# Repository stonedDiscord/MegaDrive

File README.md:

# MegaDrive
An Open-Source HardWare (OSHW) recreation of the Sega Mega Drive

The design tries to be a 1:1 recreation of the original IC BD M5 PAL board.

## Some of the planned Changes and improvements
- [ ] Verify component values
- [ ] S-Video out

## Tips if you decide to make this/get it made
The dimensions are 240x191mm.

You will have to source the 2 SEGA custom chips from either a dead board or a chip dealer.

## Roadmap:
Look at the changes in the other revisions.

## Inspired by
https://github.com/Redherring32/OpenTendo

## Credits

ArcadeTV for the stripped scans:
https://circuit-board.de/forum/index.php/Thread/13913-STRIP-CLUB-PCB-Scans/

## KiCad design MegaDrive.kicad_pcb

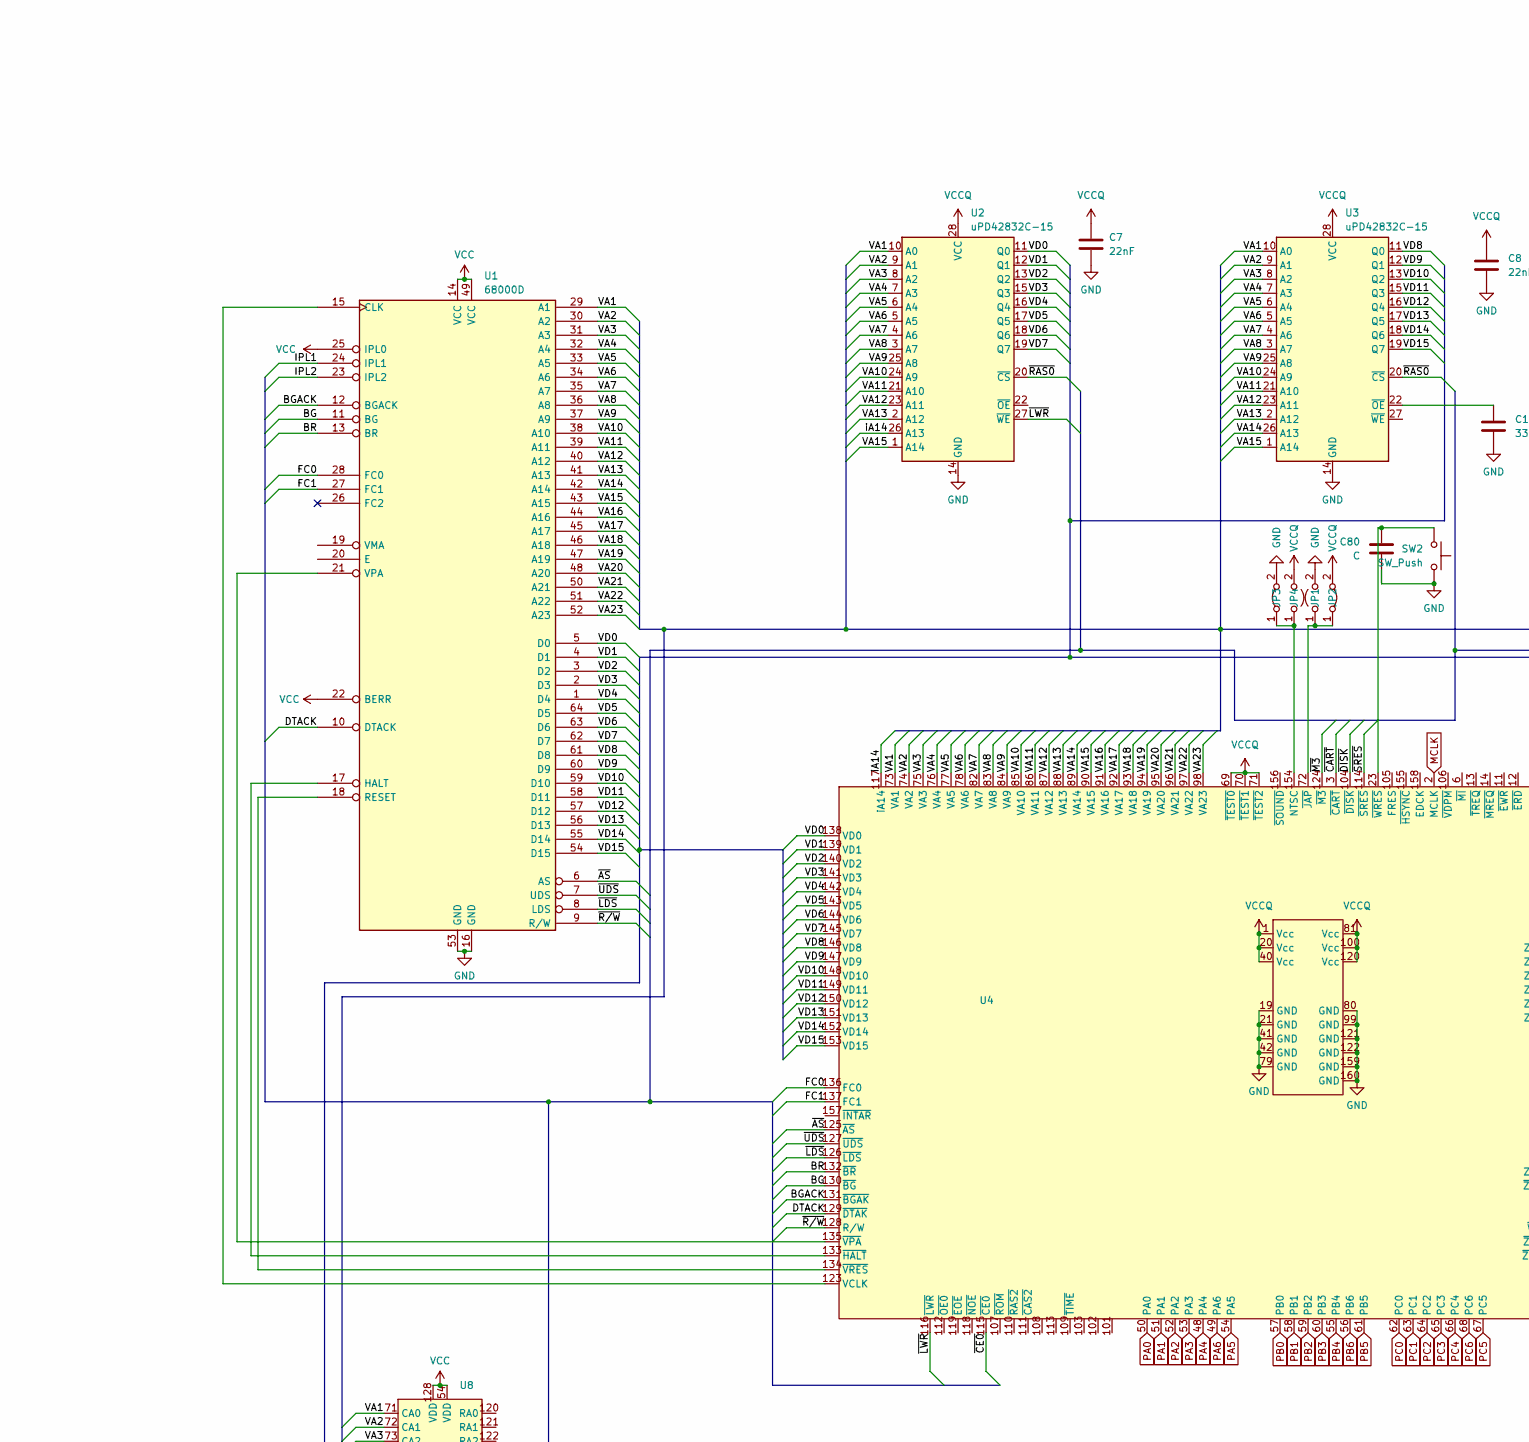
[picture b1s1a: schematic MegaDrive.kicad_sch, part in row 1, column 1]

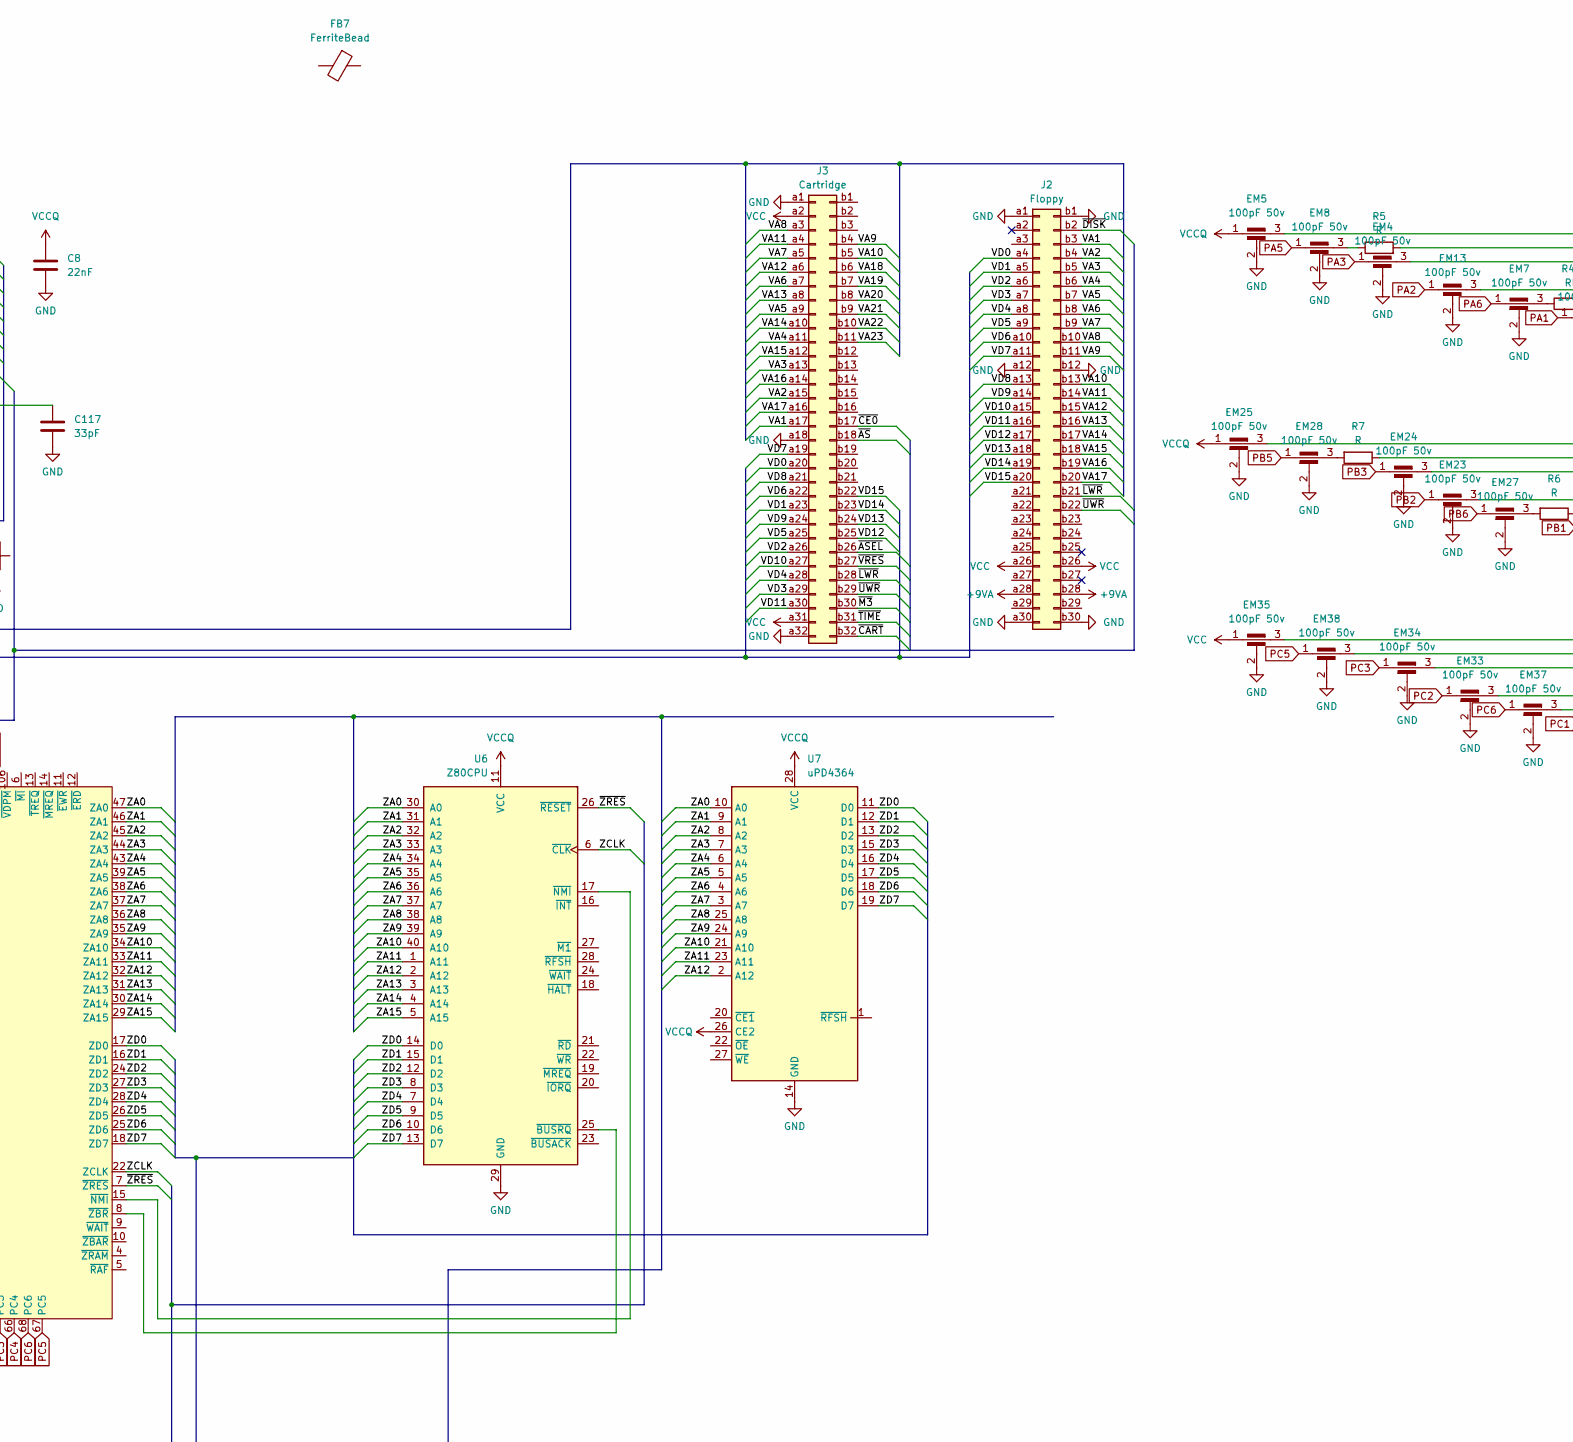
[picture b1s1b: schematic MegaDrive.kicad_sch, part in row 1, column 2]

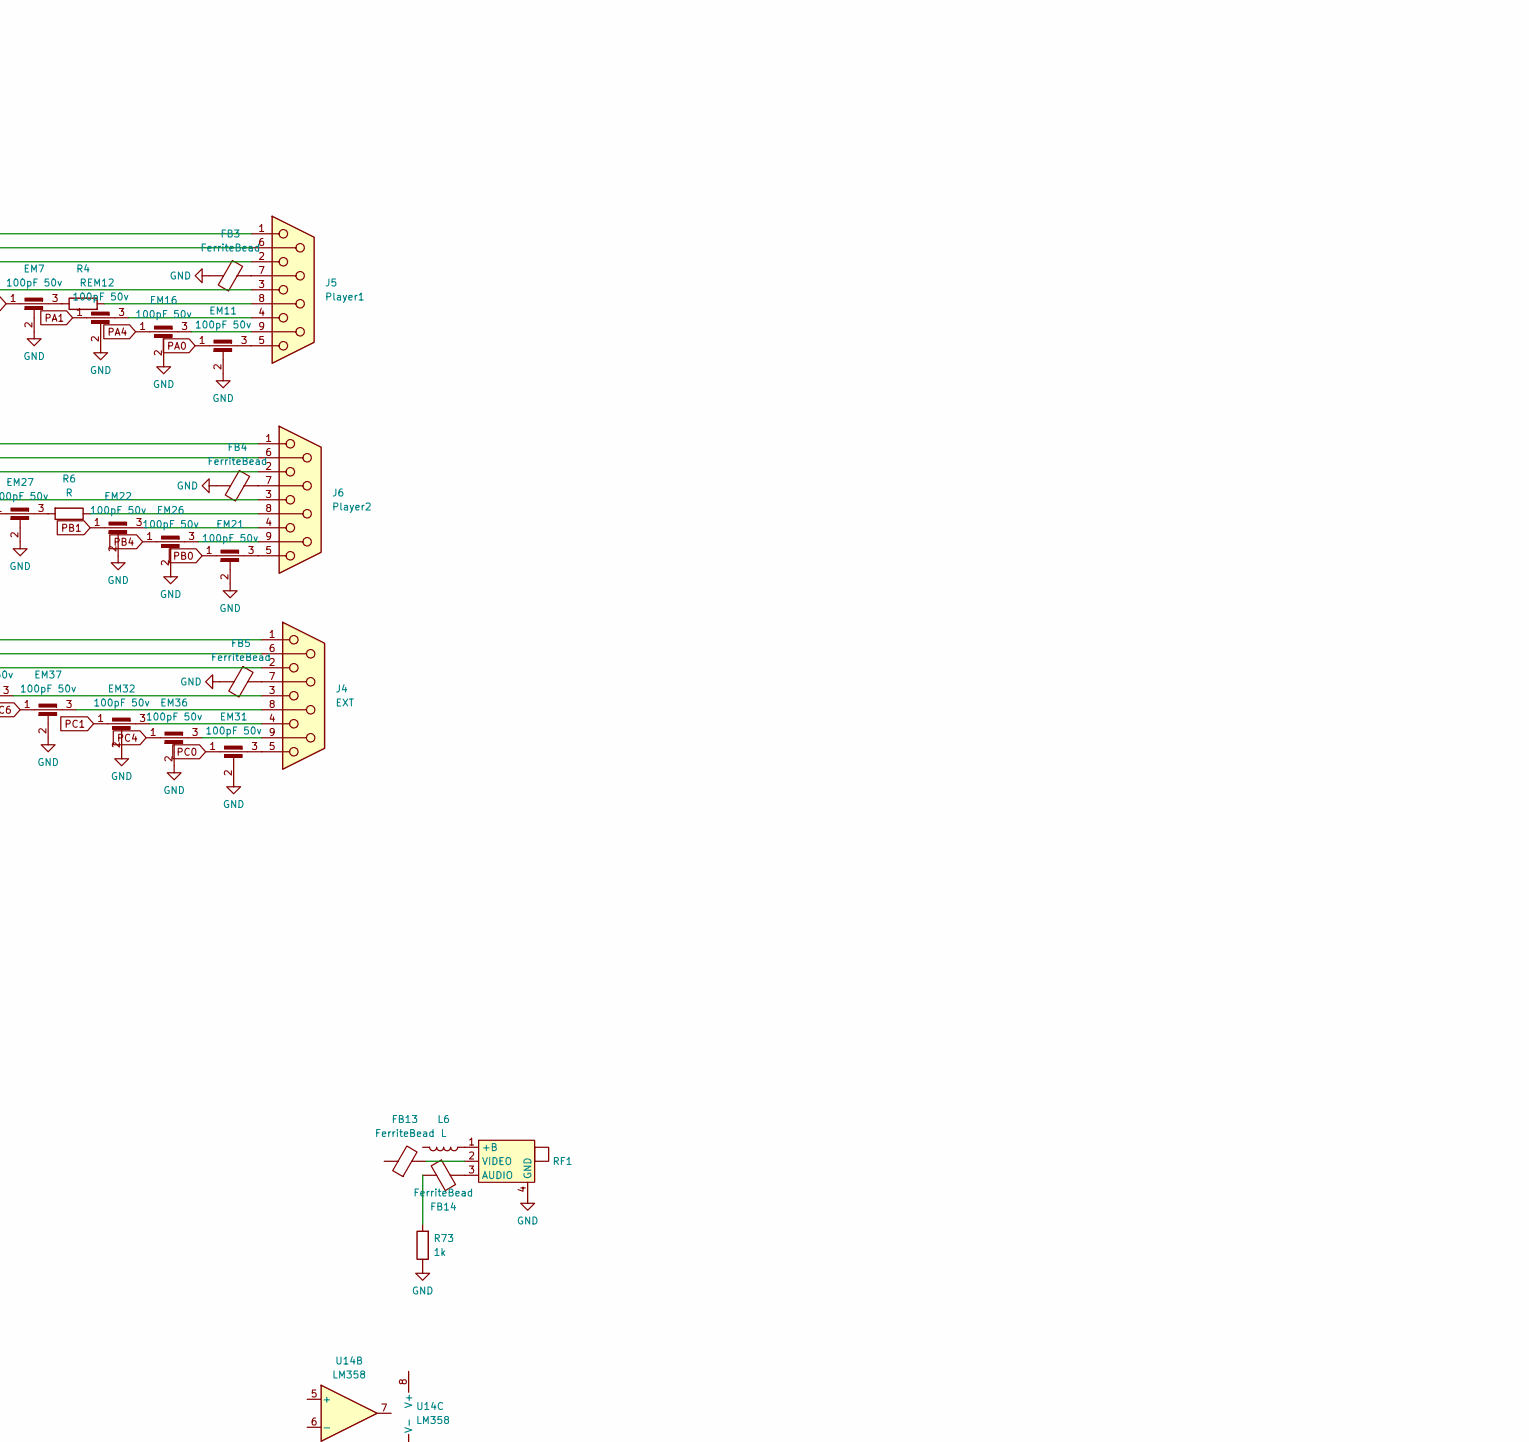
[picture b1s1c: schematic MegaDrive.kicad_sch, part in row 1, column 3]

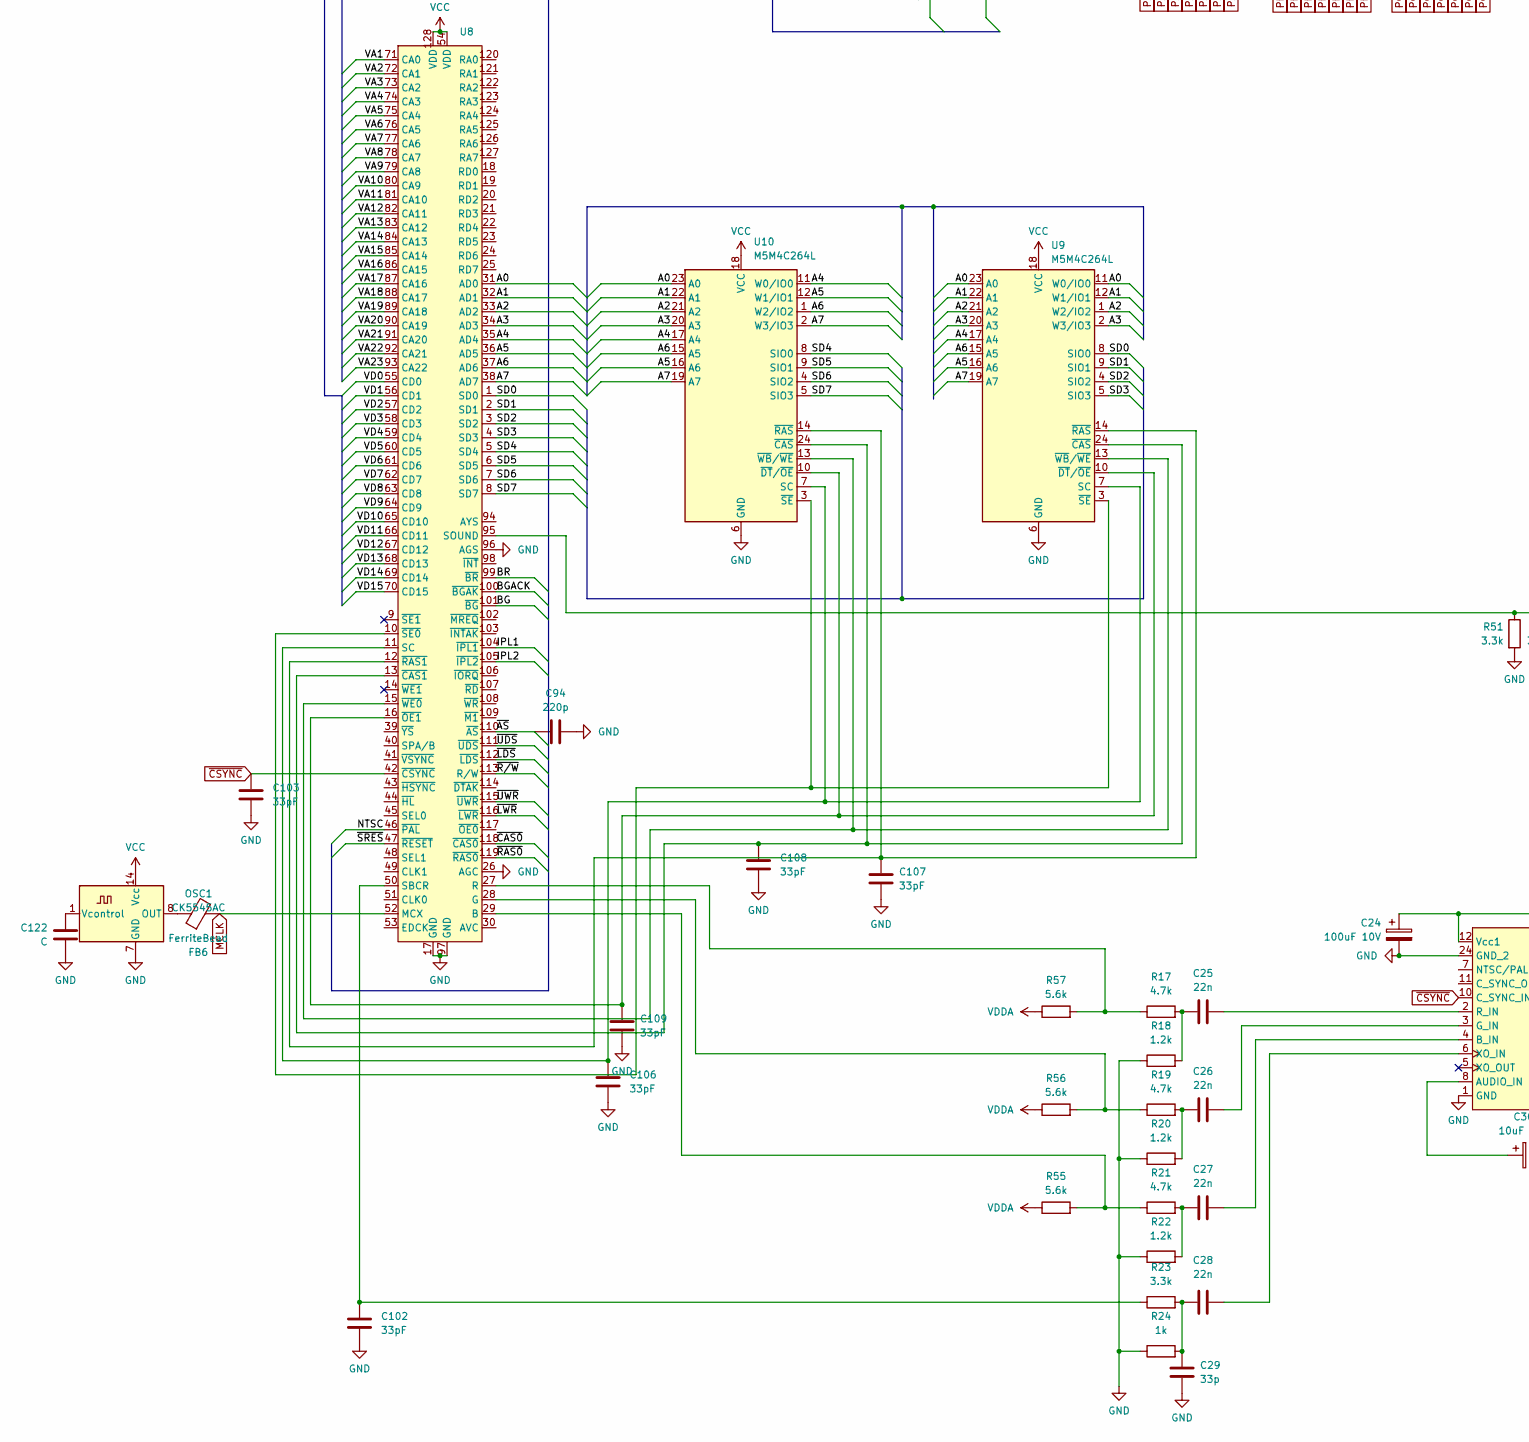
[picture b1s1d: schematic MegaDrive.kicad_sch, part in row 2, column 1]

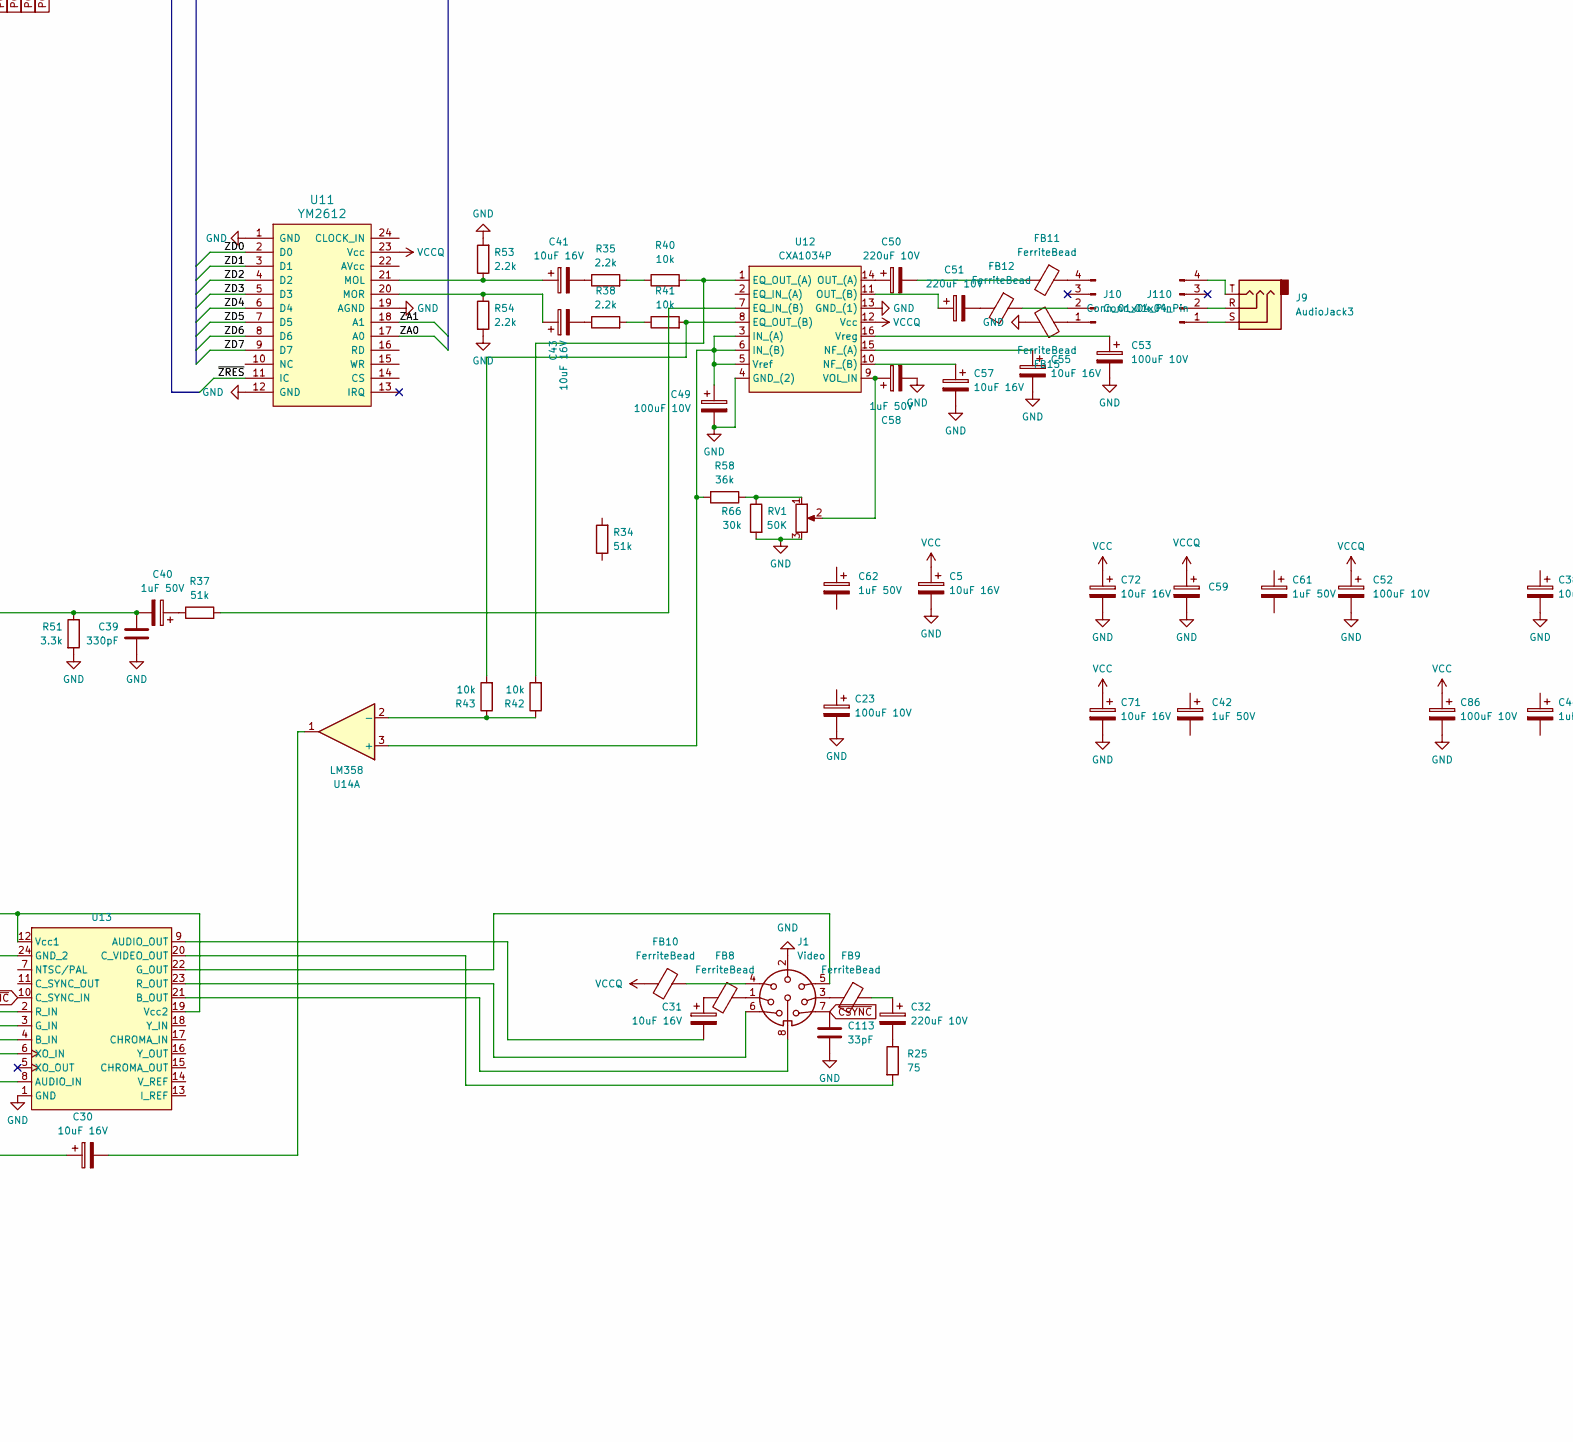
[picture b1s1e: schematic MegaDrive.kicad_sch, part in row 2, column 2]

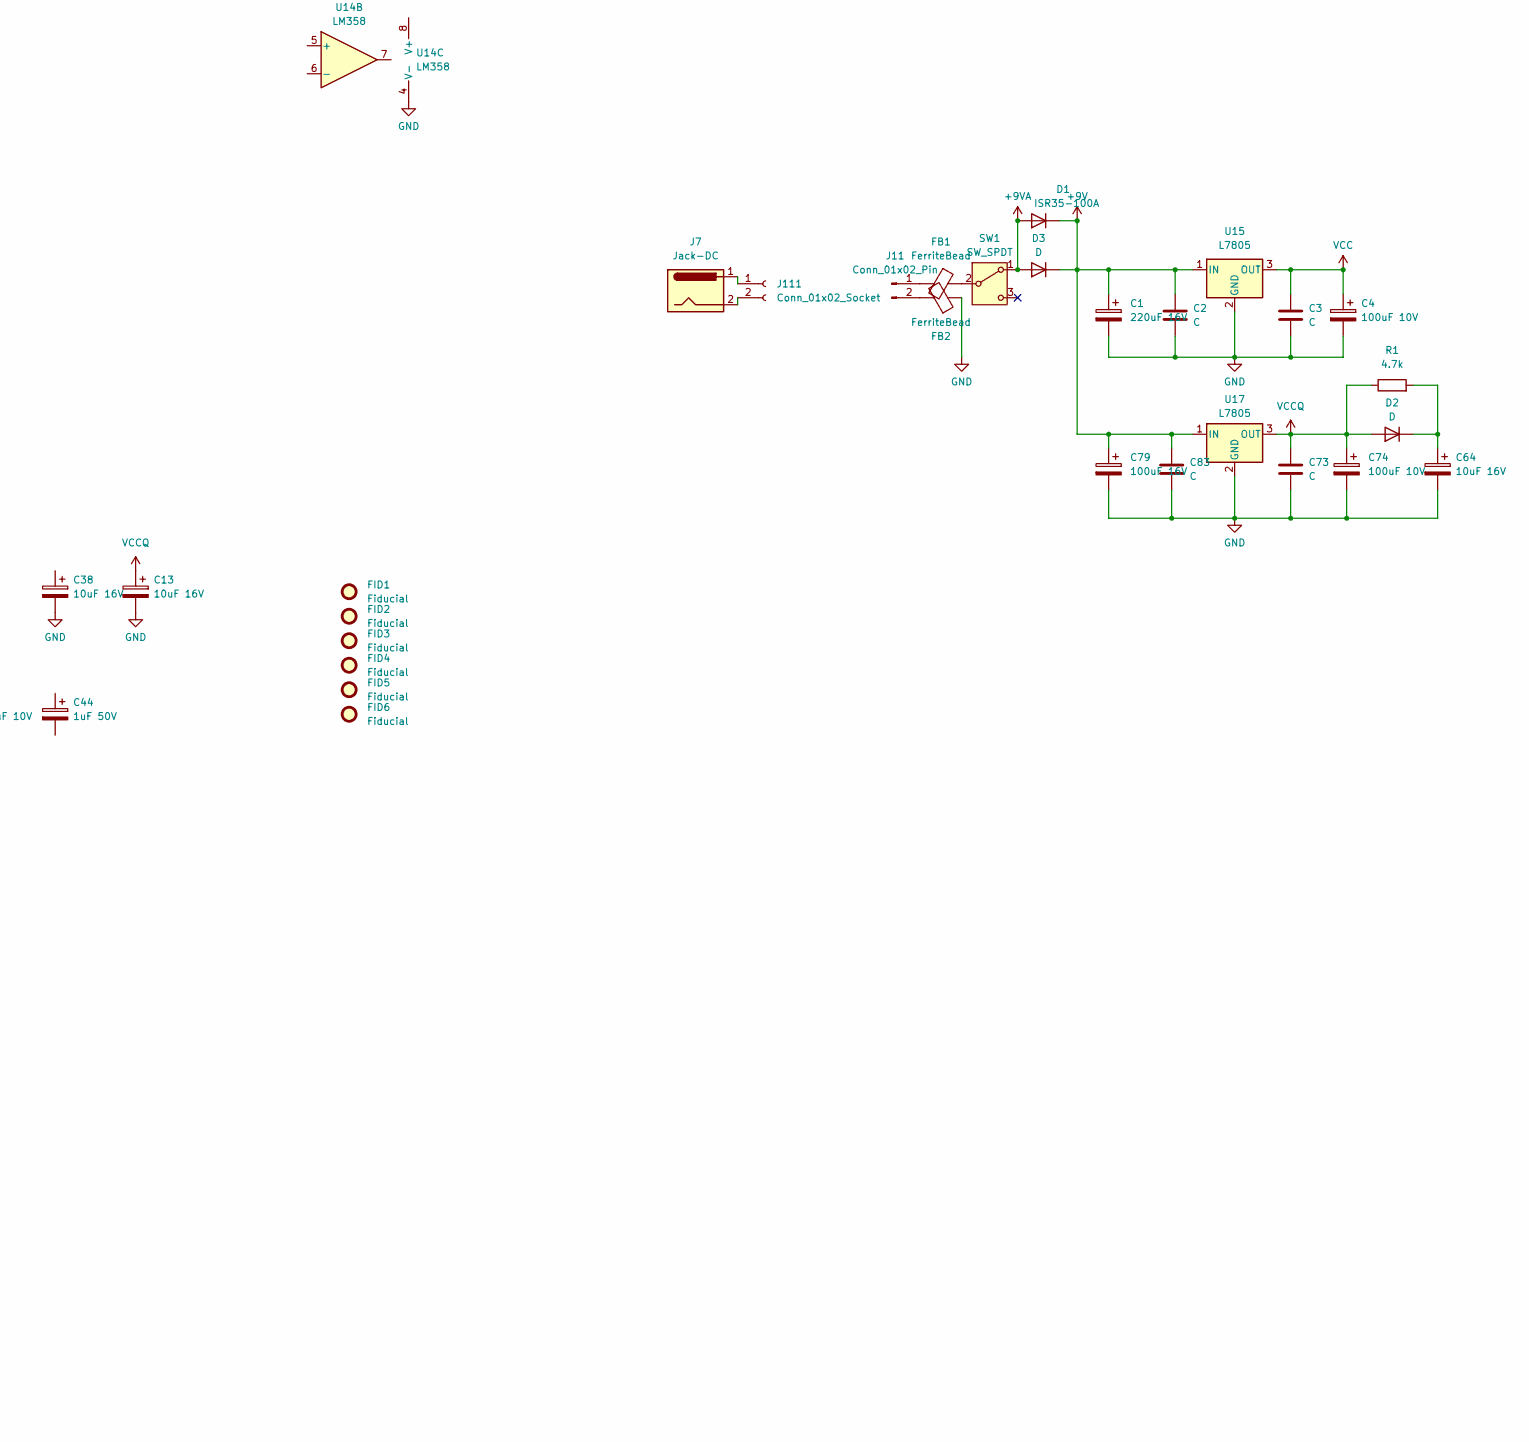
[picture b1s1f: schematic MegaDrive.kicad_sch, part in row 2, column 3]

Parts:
C1: 220uF 16V; CP_Radial_D8.0mm_P5.00mm
C2, C3, C73, C80, C83, C122: C; C_0805_2012Metric
C4, C23, C24, C49, C52, C53: 100uF 10V; CP_Radial_Tantal_D4.5mm_P5.00mm
C5, C13, C30, C31, C38, C41, C43, C55, C57, C64, C71, C72: 10uF 16V; CP_Radial_Tantal_D4.5mm_P5.00mm
C7, C8: 22nF; C_0805_2012Metric
C25, C26, C27, C28: 22n; C_0805_2012Metric
C29: 33p; C_0805_2012Metric
C32, C50, C51: 220uF 10V; CP_Radial_Tantal_D4.5mm_P5.00mm
C39: 330pF; C_0805_2012Metric
C40, C42, C44, C58, C61, C62: 1uF 50V; CP_Radial_Tantal_D4.5mm_P5.00mm
C59: CP_Radial_Tantal_D4.5mm_P5.00mm
C74, C86: 100uF 10V; CP_Radial_D8.0mm_P5.00mm
C79: 100uF 16V; CP_Radial_D8.0mm_P5.00mm
C94: 220p; C_0805_2012Metric
C102, C103, C106, C107, C108, C109, C113, C117: 33pF; C_0805_2012Metric
D1: ISR35-100A; D_A-405_P5.08mm_Vertical_AnodeUp
D2, D3: D; D_A-405_P5.08mm_Vertical_AnodeUp
EM4, EM5, EM7, EM8, EM11, EM12, EM13, EM16, EM21, EM22, EM23, EM24, EM25, EM26, EM27, EM28, EM31, EM32, EM33, EM34, EM35, EM36, EM37, EM38: 100pF 50v; Resonator-3Pin_W6.0mm_H3.0mm
FB1, FB2, FB3, FB4, FB5, FB6, FB7, FB8, FB9, FB10, FB11, FB12, FB13, FB14, FB15: FerriteBead; LairdTech_28C0236-0JW-10
FID1, FID2, FID3, FID4, FID5, FID6: Fiducial; Fiducial_1.5mm_Mask4.5mm
J1: Video; DIN8Video
J2: Floppy; Expansion
J3: Cartridge; SEGA_2x32_Female_Vertical_THT
J4: EXT; DSUB-9_Female_Horizontal_P2.77x2.54mm_EdgePinOffset9.40mm
J5: Player1; DSUB-9_Female_Horizontal_P2.77x2.54mm_EdgePinOffset9.40mm
J6: Player2; DSUB-9_Female_Horizontal_P2.77x2.54mm_EdgePinOffset9.40mm
J7: Jack-DC; JWT_A3963_1x02_P3.96mm_Vertical
J9: AudioJack3; Jack_3.5mm_CUI_SJ1-3523N_Horizontal
J10, J110: Conn_01x04_Pin; PinHeader_1x04_P2.00mm_Vertical
J11: Conn_01x02_Pin; PinHeader_1x02_P2.54mm_Vertical
J111: Conn_01x02_Socket; PinHeader_1x02_P2.54mm_Vertical
JP1: JAP; R_Axial_DIN0204_L3.6mm_D1.6mm_P5.08mm_Horizontal
JP2: ENG; R_Axial_DIN0204_L3.6mm_D1.6mm_P5.08mm_Horizontal
JP3: PAL; R_Axial_DIN0204_L3.6mm_D1.6mm_P5.08mm_Horizontal
JP4: NTSC; R_Axial_DIN0204_L3.6mm_D1.6mm_P5.08mm_Horizontal
L6: L; L_Axial_L7.0mm_D3.3mm_P5.08mm_Vertical_Fastron_MICC
OSC1: CK5545AC; Oscillator_DIP-14
R1, R17, R19, R21: 4.7k; R_0805_2012Metric
R4, R5, R6, R7: R; R_0805_2012Metric
R18, R20, R22: 1.2k; R_0805_2012Metric
R23, R51: 3.3k; R_0805_2012Metric
R24, R73: 1k; R_0805_2012Metric
R25: 75; R_0805_2012Metric
R34, R37: 51k; R_0805_2012Metric
R35, R38, R53, R54: 2.2k; R_0805_2012Metric
R40, R41, R42, R43: 10k; R_0805_2012Metric
R55, R56, R57: 5.6k; R_0805_2012Metric
R58: 36k; R_0805_2012Metric
R66: 30k; R_0805_2012Metric
RF1: RFmod
RV1: 50K
SW1: SW_SPDT; SW_E-Switch_EG1224_SPDT_Angled
SW2: SW_Push; SW_Tactile_Straight_KSA0Axx1LFTR
U1: 68000D; DIP-64_W22.86mm
U2, U3: uPD42832C-15; DIP-28_DoubleLast
U4: PQFP-160_28x28mm_P0.65mm
U6: Z80CPU; DIP-40_W15.24mm
U7: uPD4364; DIP-28_DoubleFirst
U8: QFP128
U9, U10: M5M4C264L; ZIP-24
U11: YM2612; DIP-24_W15.24mm
U12: CXA1034P; DIP-16_W7.62mm
U13: DIP-24_W10.16mm
U14: LM358; DIP-8_W7.62mm
U15, U17: L7805; TO-220-3_Vertical

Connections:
+9V: C1.1, C2.1, C79.1, C83.1, D1.1 (K), D3.1 (K), U15.1 (IN), U17.1 (IN)
+9VA: D1.2 (A), D3.2 (A), J2.a28, J2.b28, SW1.1 (A)
/A0: U8.31 (AD0), U9.11 (W0/IO0), U9.23 (A0), U10.23 (A0)
/A1: U8.32 (AD1), U9.12 (W1/IO1), U9.22 (A1), U10.22 (A1)
/A2: U8.33 (AD2), U9.1 (W2/IO2), U9.21 (A2), U10.21 (A2)
/A3: U8.34 (AD3), U9.2 (W3/IO3), U9.20 (A3), U10.20 (A3)
/A4: U8.35 (AD4), U9.17 (A4), U10.11 (W0/IO0), U10.17 (A4)
/A5: U8.36 (AD5), U9.16 (A6), U10.12 (W1/IO1), U10.16 (A6)
/A6: U8.37 (AD6), U9.15 (A5), U10.1 (W2/IO2), U10.15 (A5)
/A7: U8.38 (AD7), U9.19 (A7), U10.2 (W3/IO3), U10.19 (A7)
/BG: U1.11 (BG), U4.130 (~BG), U8.101 (~BG)
/BGACK: U1.12 (BGACK), U4.131 (~BGAK), U8.100 (~BGAK)
/BR: U1.13 (BR), U4.132 (~BR), U8.99 (~BR)
/DTACK: U1.10 (DTACK), U4.129 (~DTAK)
/FC0: U1.28 (FC0), U4.136 (FC0)
/FC1: U1.27 (FC1), U4.137 (FC1)
/IPL1: U1.24 (IPL1), U8.104 (~IPL1)
/IPL2: U1.23 (IPL2), U8.105 (~IPL2)
/NTSC: U8.46 (~PAL)
/SD0: U8.1 (SD0), U9.8 (SIO0)
/SD1: U8.2 (SD1), U9.9 (SIO1)
/SD2: U8.3 (SD2), U9.4 (SIO2)
/SD3: U8.4 (SD3), U9.5 (SIO3)
/SD4: U8.5 (SD4), U10.8 (SIO0)
/SD5: U8.6 (SD5), U10.9 (SIO1)
/SD6: U8.7 (SD6), U10.4 (SIO2)
/SD7: U8.8 (SD7), U10.5 (SIO3)
/VA1: J2.b3, J3.a17, U1.29 (A1), U2.10 (A0), U3.10 (A0), U4.73 (VA1), U8.71 (CA0)
/VA2: J2.b4, J3.a15, U1.30 (A2), U2.9 (A1), U3.9 (A1), U4.74 (VA2), U8.72 (CA1)
/VA3: J2.b5, J3.a13, U1.31 (A3), U2.8 (A2), U3.8 (A2), U4.75 (VA3), U8.73 (CA2)
/VA4: J2.b6, J3.a11, U1.32 (A4), U2.7 (A3), U3.7 (A3), U4.76 (VA4), U8.74 (CA3)
/VA5: J2.b7, J3.a9, U1.33 (A5), U2.6 (A4), U3.6 (A4), U4.77 (VA5), U8.75 (CA4)
/VA6: J2.b8, J3.a7, U1.34 (A6), U2.5 (A5), U3.5 (A5), U4.78 (VA6), U8.76 (CA5)
/VA7: J2.b9, J3.a5, U1.35 (A7), U2.4 (A6), U3.4 (A6), U4.82 (VA7), U8.77 (CA6)
/VA8: J2.b10, J3.a3, U1.36 (A8), U2.3 (A7), U3.3 (A7), U4.83 (VA8), U8.78 (CA7)
/VA9: J2.b11, J3.b4, U1.37 (A9), U2.25 (A8), U3.25 (A8), U4.84 (VA9), U8.79 (CA8)
/VA10: J2.b13, J3.b5, U1.38 (A10), U2.24 (A9), U3.24 (A9), U4.85 (VA10), U8.80 (CA9)
/VA11: J2.b14, J3.a4, U1.39 (A11), U2.21 (A10), U3.21 (A10), U4.86 (VA11), U8.81 (CA10)
/VA12: J2.b15, J3.a6, U1.40 (A12), U2.23 (A11), U3.23 (A11), U4.87 (VA12), U8.82 (CA11)
/VA13: J2.b16, J3.a8, U1.41 (A13), U2.2 (A12), U3.2 (A12), U4.88 (VA13), U8.83 (CA12)
/VA14: J2.b17, J3.a10, U1.42 (A14), U3.26 (A13), U4.89 (VA14), U8.84 (CA13)
/VA15: J2.b18, J3.a12, U1.43 (A15), U2.1 (A14), U3.1 (A14), U4.90 (VA15), U8.85 (CA14)
/VA16: J2.b19, J3.a14, U1.44 (A16), U4.91 (VA16), U8.86 (CA15)
/VA17: J2.b20, J3.a16, U1.45 (A17), U4.92 (VA17), U8.87 (CA16)
/VA18: J3.b6, U1.46 (A18), U4.93 (VA18), U8.88 (CA17)
/VA19: J3.b7, U1.47 (A19), U4.94 (VA19), U8.89 (CA18)
/VA20: J3.b8, U1.48 (A20), U4.95 (VA20), U8.90 (CA19)
/VA21: J3.b9, U1.50 (A21), U4.96 (VA21), U8.91 (CA20)
/VA22: J3.b10, U1.51 (A22), U4.97 (VA22), U8.92 (CA21)
/VA23: J3.b11, U1.52 (A23), U4.98 (VA23), U8.93 (CA22)
/VD0: J2.a4, J3.a20, U1.5 (D0), U2.11 (Q0), U4.138 (VD0), U8.55 (CD0)
/VD1: J2.a5, J3.a23, U1.4 (D1), U2.12 (Q1), U4.139 (VD1), U8.56 (CD1)
/VD2: J2.a6, J3.a26, U1.3 (D2), U2.13 (Q2), U4.140 (VD2), U8.57 (CD2)
/VD3: J2.a7, J3.a29, U1.2 (D3), U2.15 (Q3), U4.141 (VD3), U8.58 (CD3)
/VD4: J2.a8, J3.a28, U1.1 (D4), U2.16 (Q4), U4.142 (VD4), U8.59 (CD4)
/VD5: J2.a9, J3.a25, U1.64 (D5), U2.17 (Q5), U4.143 (VD5), U8.60 (CD5)
/VD6: J2.a10, J3.a22, U1.63 (D6), U2.18 (Q6), U4.144 (VD6), U8.61 (CD6)
/VD7: J2.a11, J3.a19, U1.62 (D7), U2.19 (Q7), U4.145 (VD7), U8.62 (CD7)
/VD8: J2.a13, J3.a21, U1.61 (D8), U3.11 (Q0), U4.146 (VD8), U8.63 (CD8)
/VD9: J2.a14, J3.a24, U1.60 (D9), U3.12 (Q1), U4.147 (VD9), U8.64 (CD9)
/VD10: J2.a15, J3.a27, U1.59 (D10), U3.13 (Q2), U4.148 (VD10), U8.65 (CD10)
/VD11: J2.a16, J3.a30, U1.58 (D11), U3.15 (Q3), U4.149 (VD11), U8.66 (CD11)
/VD12: J2.a17, J3.b25, U1.57 (D12), U3.16 (Q4), U4.150 (VD12), U8.67 (CD12)
/VD13: J2.a18, J3.b24, U1.56 (D13), U3.17 (Q5), U4.151 (VD13), U8.68 (CD13)
/VD14: J2.a19, J3.b23, U1.55 (D14), U3.18 (Q6), U4.152 (VD14), U8.69 (CD14)
/VD15: J2.a20, J3.b22, U1.54 (D15), U3.19 (Q7), U4.153 (VD15), U8.70 (CD15)
/ZA0: U4.47 (ZA0), U6.30 (A0), U7.10 (A0), U11.17 (A0)
/ZA1: U4.46 (ZA1), U6.31 (A1), U7.9 (A1), U11.18 (A1)
/ZA2: U4.45 (ZA2), U6.32 (A2), U7.8 (A2)
/ZA3: U4.44 (ZA3), U6.33 (A3), U7.7 (A3)
/ZA4: U4.43 (ZA4), U6.34 (A4), U7.6 (A4)
/ZA5: U4.39 (ZA5), U6.35 (A5), U7.5 (A5)
/ZA6: U4.38 (ZA6), U6.36 (A6), U7.4 (A6)
/ZA7: U4.37 (ZA7), U6.37 (A7), U7.3 (A7)
/ZA8: U4.36 (ZA8), U6.38 (A8), U7.25 (A8)
/ZA9: U4.35 (ZA9), U6.39 (A9), U7.24 (A9)
/ZA10: U4.34 (ZA10), U6.40 (A10), U7.21 (A10)
/ZA11: U4.33 (ZA11), U6.1 (A11), U7.23 (A11)
/ZA12: U4.32 (ZA12), U6.2 (A12), U7.2 (A12)
/ZA13: U4.31 (ZA13), U6.3 (A13)
/ZA14: U4.30 (ZA14), U6.4 (A14)
/ZA15: U4.29 (ZA15), U6.5 (A15)
/ZCLK: U4.22 (ZCLK), U6.6 (~CLK)
/ZD0: U4.17 (ZD0), U6.14 (D0), U7.11 (D0), U11.2 (D0)
/ZD1: U4.16 (ZD1), U6.15 (D1), U7.12 (D1), U11.3 (D1)
/ZD2: U4.24 (ZD2), U6.12 (D2), U7.13 (D2), U11.4 (D2)
/ZD3: U4.27 (ZD3), U6.8 (D3), U7.15 (D3), U11.5 (D3)
/ZD4: U4.28 (ZD4), U6.7 (D4), U7.16 (D4), U11.6 (D4)
/ZD5: U4.26 (ZD5), U6.9 (D5), U7.17 (D5), U11.7 (D5)
/ZD6: U4.25 (ZD6), U6.10 (D6), U7.18 (D6), U11.8 (D6)
/ZD7: U4.18 (ZD7), U6.13 (D7), U7.19 (D7), U11.9 (D7)
/iA14: U2.26 (A13), U4.117 (iA14)
/~ASEL: J3.b26
/~AS: C94.2, J3.b18, U1.6 (AS), U4.125 (~AS), U8.110 (~AS)
/~CART: J3.b32, U4.3 (~CART)
/~CAS0: U8.118 (~CAS0)
/~CE0: J3.b17, U4.115 (~CE0)
/~DISK: J2.b2, U4.104 (~DISK)
/~LDS: U1.8 (LDS), U4.126 (~LDS), U8.112 (~LDS)
/~LWR: J2.b21, J3.b28, U2.27 (~WE), U4.116 (~LWR), U8.116 (~LWR)
/~M3: J3.b30, U4.124 (~M3)
/~RAS0: U2.20 (~CS), U3.20 (~CS), U8.119 (~RAS0)
/~R/W: U1.9 (R/W), U4.128 (R/W), U8.113 (R/W)
/~SRES: U4.114 (~SRES), U8.47 (~RESET)
/~TIME: J3.b31
/~UDS: U1.7 (UDS), U4.127 (~UDS), U8.111 (~UDS)
/~UWR: J2.b22, J3.b29, U8.115 (~UWR)
/~VRES: J3.b27
/~ZRES: U4.7 (~ZRES), U6.26 (~RESET), U11.11 (IC)
GND: C1.2, C2.2, C3.2, C4.2, C5.2, C7.2, C8.2, C13.2, C23.2, C24.2, C29.2, C38.2, C39.2, C49.2, C52.2, C53.2, C55.2, C57.2, C58.2, C59.2, C64.2, C71.2, C72.2, C73.2, C74.2, C79.2, C80.2, C83.2, C86.2, C94.1, C102.2, C103.2, C106.2, C107.2, C108.2, C109.2, C113.2, C117.2, C122.2, EM4.2, EM5.2, EM7.2, EM8.2, EM11.2, EM12.2, EM13.2, EM16.2, EM21.2, EM22.2, EM23.2, EM24.2, EM25.2, EM26.2, EM27.2, EM28.2, EM31.2, EM32.2, EM33.2, EM34.2, EM35.2, EM36.2, EM37.2, EM38.2, FB2.1, FB3.2, FB4.2, FB5.2, FB15.2, J1.2, J2.a1, J2.a12, J2.a30, J2.b1, J2.b12, J2.b30, J3.a1, J3.a18, J3.a32, JP1.2 (B), JP3.2 (B), OSC1.7 (GND), R18.1, R20.1, R22.1, R24.1, R51.2, R53.2, R54.2, R66.2, R73.1, RF1.4 (GND), RV1.3, SW2.1, U1.16 (GND), U1.53 (GND), U2.14 (GND), U3.14 (GND), U4.19 (GND), U4.21 (GND), U4.41 (GND), U4.42 (GND), U4.79 (GND), U4.80 (GND), U4.99 (GND), U4.121 (GND), U4.122 (GND), U4.159 (GND), U4.160 (GND), U6.29 (GND), U7.14 (GND), U8.17 (GND), U8.26 (AGC), U8.96 (AGS), U8.97 (GND), U9.6 (GND), U10.6 (GND), U11.1 (GND), U11.12 (GND), U11.19 (AGND), U12.4 (GND_(2)), U12.13 (GND_(1)), U13.1 (GND), U13.24 (GND_2), U14.4 (V-), U15.2 (GND), U17.2 (GND)
MCLK: FB6.2, U4.2 (MCLK), U8.52 (MCX)
unnamed: C25.1, R17.2, R18.2
unnamed: C26.1, R19.2, R20.2
unnamed: C27.1, R21.2, R22.2
unnamed: C28.2, C29.1, R23.2, R24.2
unnamed: C30.2, U14.1
unnamed: C31.1, FB8.2
unnamed: C32.1, FB9.1
unnamed: C32.2, R25.1
unnamed: C40.1, R37.1
unnamed: C41.2, R35.1
unnamed: C43.2, R38.1
unnamed: C50.2, FB11.2
unnamed: C51.2, FB12.2
unnamed: C64.1, D2.1 (K), R1.2
unnamed: EM4.3, J5.2
unnamed: EM5.3, J5.1
unnamed: EM7.3, R4.1
unnamed: EM8.3, R5.1
unnamed: EM11.3, J5.5
unnamed: EM12.3, J5.4
unnamed: EM13.3, J5.3
unnamed: EM16.3, J5.9
unnamed: EM21.3, J6.5
unnamed: EM22.3, J6.4
unnamed: EM23.3, J6.3
unnamed: EM24.3, J6.2
unnamed: EM25.3, J6.1
unnamed: EM26.3, J6.9
unnamed: EM27.3, R6.2
unnamed: EM28.3, R7.2
unnamed: EM31.3, J4.5
unnamed: EM32.3, J4.4
unnamed: EM33.3, J4.3
unnamed: EM34.3, J4.2
unnamed: EM35.3, J4.1
unnamed: EM36.3, J4.9
unnamed: EM37.3, J4.8
unnamed: EM38.3, J4.6
unnamed: FB3.1, J5.7
unnamed: FB4.1, J6.7
unnamed: FB5.1, J4.7
unnamed: FB8.1, J1.1
unnamed: FB9.2, J1.3
unnamed: FB10.1, J1.4
unnamed: FB14.1, R73.2
unnamed: J5.6, R5.2
unnamed: J5.8, R4.2
unnamed: J6.6, R7.1
unnamed: J6.8, R6.1
unnamed: FB15.1, J10.1
unnamed: FB12.1, J10.2
unnamed: FB11.1, J10.4
unnamed: FB1.2, J11.1
unnamed: FB2.2, J11.2
unnamed: J9.S, J110.1
unnamed: J9.R, J110.2
unnamed: J9.T, J110.4
unnamed: J7.1, J111.1
unnamed: J7.2, J111.2
unnamed: JP1.1 (A), JP2.1 (A), U4.72 (~JAP)
unnamed: JP3.1 (A), JP4.1 (A), U4.154 (NTSC)
unnamed: FB6.1, OSC1.8 (OUT)
unnamed: C122.1, OSC1.1 (Vcontrol)
unnamed: R35.2, R40.1
unnamed: R38.2, R41.1
unnamed: R58.1, R66.1, RV1.1
unnamed: L6.2, RF1.1 (+B)
unnamed: FB14.2, RF1.3 (AUDIO)
unnamed: FB13.2, RF1.2 (VIDEO)
unnamed: FB1.1, SW1.2 (B)
unnamed: U1.15 (CLK), U4.123 (VCLK)
unnamed: U1.17 (HALT), U4.133 (~HALT)
unnamed: U1.18 (RESET), U4.134 (~VRES)
unnamed: U1.21 (VPA), U4.135 (~VPA)
unnamed: C117.1, U3.22 (~OE)
unnamed: U4.15 (~NMI), U6.17 (~NMI)
unnamed: C80.1, SW2.2, U4.23 (~WRES)
unnamed: U4.8 (~ZBR), U6.25 (~BUSRQ)
unnamed: R21.1, R55.2, U8.29 (B)
unnamed: R19.1, R56.2, U8.28 (G)
unnamed: R17.1, R57.2, U8.27 (R)
unnamed: C102.1, R23.1, U8.50 (SBCR)
unnamed: C39.1, C40.2, R51.1, U8.95 (SOUND)
unnamed: C106.1, U8.11 (SC), U9.7 (SC), U10.7 (SC)
unnamed: C108.1, U8.13 (~CAS1), U9.24 (~CAS), U10.24 (~CAS)
unnamed: C109.1, U8.16 (~OE1), U9.10 (~DT/~OE), U10.10 (~DT/~OE)
unnamed: C107.1, U8.12 (~RAS1), U9.14 (~RAS), U10.14 (~RAS)
unnamed: U8.10 (~SE0), U9.3 (~SE), U10.3 (~SE)
unnamed: U8.15 (~WE0), U9.13 (~WB/~WE), U10.13 (~WB/~WE)
unnamed: C41.1, R53.1, U11.21 (MOL)
unnamed: C43.1, R54.1, U11.20 (MOR)
unnamed: R37.2, U12.7 (EQ_IN_(B))
unnamed: R40.2, R42.2, U12.1 (EQ_OUT_(A))
unnamed: R41.2, R43.2, U12.8 (EQ_OUT_(B))
unnamed: C49.1, R58.2, U12.3 (IN_(A)), U12.5 (Vref), U12.6 (IN_(B)), U14.3 (+)
unnamed: C55.1, U12.15 (NF_(A))
unnamed: C57.1, U12.10 (NF_(B))
unnamed: C50.1, U12.14 (OUT_(A))
unnamed: C51.1, U12.11 (OUT_(B))
unnamed: C58.1, RV1.2, U12.9 (VOL_IN)
unnamed: C53.1, U12.16 (Vreg)
unnamed: C30.1, U13.8 (AUDIO_IN)
unnamed: C31.2, U13.9 (AUDIO_OUT)
unnamed: C27.2, U13.4 (B_IN)
unnamed: J1.8, U13.21 (B_OUT)
unnamed: R25.2, U13.20 (C_VIDEO_OUT)
unnamed: C26.2, U13.3 (G_IN)
unnamed: J1.5, U13.22 (G_OUT)
unnamed: C25.2, U13.2 (R_IN)
unnamed: J1.6, U13.23 (R_OUT)
unnamed: C24.1, U13.12 (Vcc1), U13.19 (Vcc2)
unnamed: C28.1, U13.6 (XO_IN)
unnamed: R42.1, R43.1, U14.2 (-)
PA0: EM11.1, U4.50 (PA0)
PA1: EM12.1, U4.51 (PA1)
PA2: EM13.1, U4.52 (PA2)
PA3: EM4.1, U4.53 (PA3)
PA4: EM16.1, U4.48 (PA4)
PA5: EM8.1, U4.54 (PA5)
PA6: EM7.1, U4.49 (PA6)
PB0: EM21.1, U4.57 (PB0)
PB1: EM22.1, U4.58 (PB1)
PB2: EM23.1, U4.59 (PB2)
PB3: EM24.1, U4.60 (PB3)
PB4: EM26.1, U4.55 (PB4)
PB5: EM28.1, U4.61 (PB5)
PB6: EM27.1, U4.56 (PB6)
PC0: EM31.1, U4.62 (PC0)
PC1: EM32.1, U4.63 (PC1)
PC2: EM33.1, U4.64 (PC2)
PC3: EM34.1, U4.65 (PC3)
PC4: EM36.1, U4.66 (PC4)
PC5: EM38.1, U4.67 (PC5)
PC6: EM37.1, U4.68 (PC6)
VCC: C3.1, C4.1, C5.1, C71.1, C72.1, C86.1, EM35.1, J2.a26, J2.b26, J3.a2, J3.a31, OSC1.14 (Vcc), U1.14 (VCC), U1.22 (BERR), U1.25 (IPL0), U1.49 (VCC), U8.54 (VDD), U8.128 (VDD), U9.18 (VCC), U10.18 (VCC), U15.3 (OUT)
VCCQ: C7.1, C8.1, C13.1, C52.1, C59.1, C73.1, C74.1, D2.2 (A), EM5.1, EM25.1, FB10.2, JP2.2 (B), JP4.2 (B), R1.1, U2.28 (VCC), U3.28 (VCC), U4.1 (Vcc), U4.20 (Vcc), U4.40 (Vcc), U4.69 (~TEST0), U4.70 (~TEST1), U4.71 (~TEST2), U4.81 (Vcc), U4.100 (Vcc), U4.120 (Vcc), U6.11 (VCC), U7.26 (CE2), U7.28 (VCC), U11.23 (Vcc), U12.12 (Vcc), U17.3 (OUT)
VDDA: R55.1, R56.1, R57.1
~CSYNC: C103.1, C113.1, J1.7, U8.42 (~CSYNC), U13.10 (C_SYNC_IN)
